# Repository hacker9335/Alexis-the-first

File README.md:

# Alexis the First

### Inspiration
I wanted to create a macropad that could help me access shortcuts I use commonly more easily. To assist with that, I added 6 keys, a rotary encoder, and some RGB for fun.

### Challenges
This was my first time using KiCad, and I had some fun figuring out how to properly use it.

### Specifications

#### BOM:
- 6x Cherry MX Switches
- 4x SK6812 MINI LEDs
- 1x Seeed XIAO RP2040
- 1x EC11 Rotary Encoder
- 6x Blank DSA Keycaps
- 4x M3x16 Bolts
- 4x M3 Heatset Inserts

#### Other Files:
- KMK Firmware (`Firmware/main.py`)
- Top Plate (`CAD/top_plate.3MF`)
- Bottom Plate (`CAD/bottom_plate.3MF`)
- Full Model Mockup (`CAD/Alexis_the_first_full.STEP`)

---

### Screenshots

| Schematic | PCB | Case |
|:---------:|:---:|:----:|
|  |  |  |

---

### Notes
- All design files are organized in their respective folders: `CAD/`, `PCB/`, `Firmware/`.
- The project uses only approved parts and fits within the required dimensions.

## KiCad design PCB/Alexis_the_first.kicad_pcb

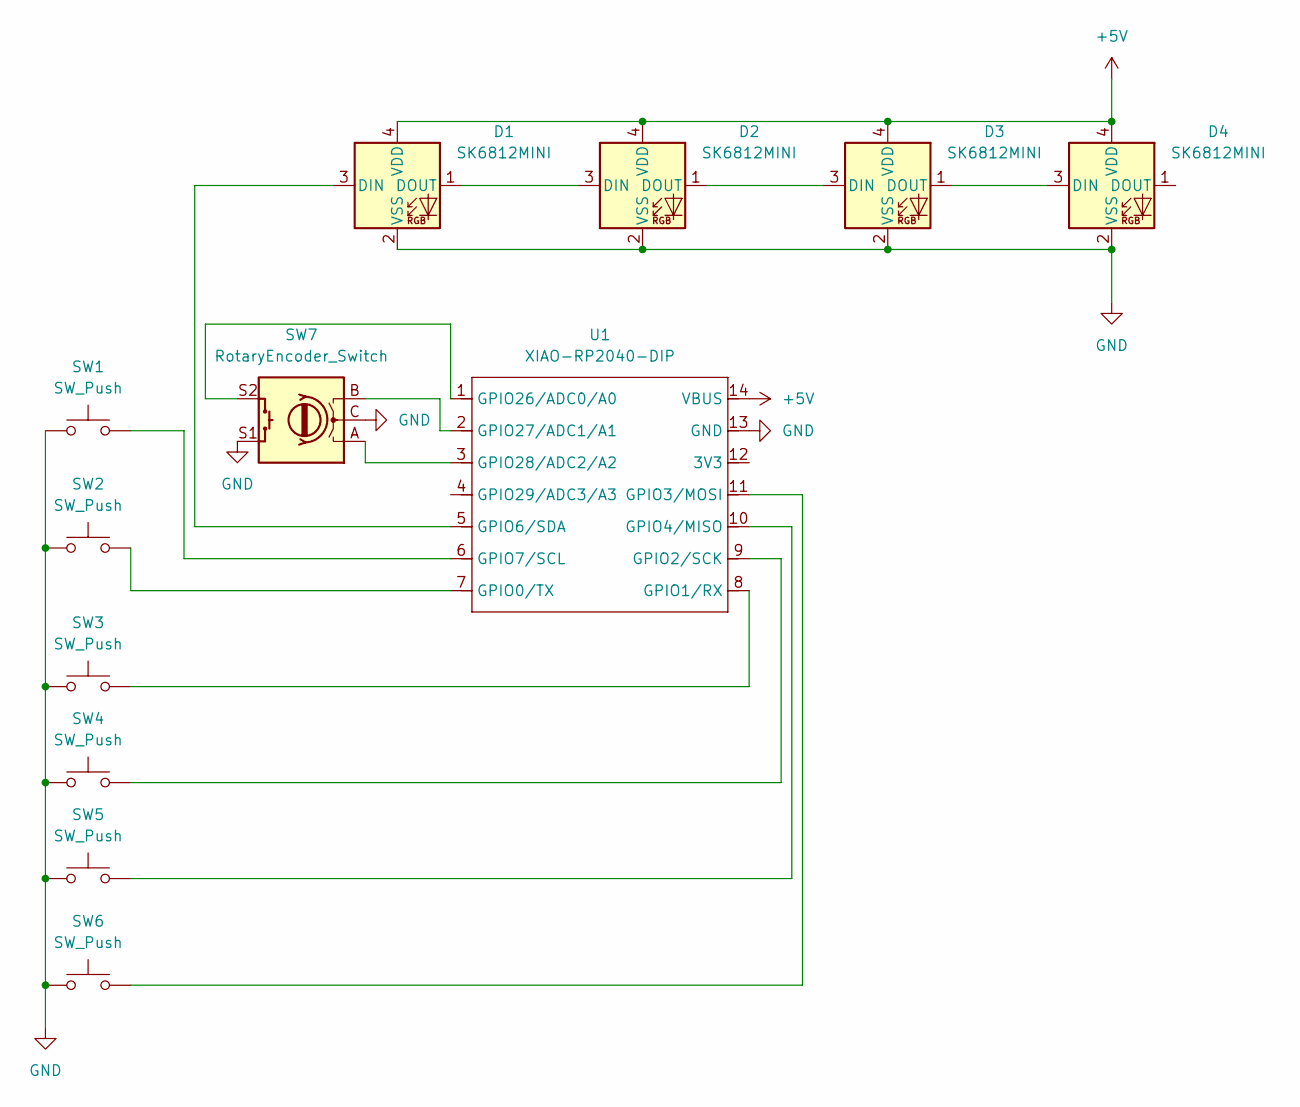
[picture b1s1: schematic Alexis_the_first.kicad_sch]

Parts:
D1, D2, D3, D4: SK6812MINI; LED_SK6812MINI_PLCC4_3.5x3.5mm_P1.75mm
SW1, SW2, SW3, SW4, SW5, SW6: SW_Push; SW_Cherry_MX_1.00u_PCB
SW7: RotaryEncoder_Switch; RotaryEncoder_Alps_EC11E-Switch_Vertical_H20mm
U1: XIAO-RP2040-DIP

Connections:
+5V: D1.4 (VDD), D2.4 (VDD), D3.4 (VDD), D4.4 (VDD), U1.14 (VBUS)
GND: D1.2 (VSS), D2.2 (VSS), D3.2 (VSS), D4.2 (VSS), SW1.1, SW2.1, SW3.1, SW4.1, SW5.1, SW6.1, SW7.C, SW7.S1, U1.13 (GND)
unnamed: D1.3 (DIN), U1.5 (GPIO6/SDA)
unnamed: D1.1 (DOUT), D2.3 (DIN)
unnamed: D2.1 (DOUT), D3.3 (DIN)
unnamed: D3.1 (DOUT), D4.3 (DIN)
unnamed: SW2.2, U1.7 (GPIO0/TX)
unnamed: SW3.2, U1.8 (GPIO1/RX)
unnamed: SW4.2, U1.9 (GPIO2/SCK)
unnamed: SW6.2, U1.11 (GPIO3/MOSI)
unnamed: SW5.2, U1.10 (GPIO4/MISO)
unnamed: SW1.2, U1.6 (GPIO7/SCL)
unnamed: SW7.S2, U1.1 (GPIO26/ADC0/A0)
unnamed: SW7.B, U1.2 (GPIO27/ADC1/A1)
unnamed: SW7.A, U1.3 (GPIO28/ADC2/A2)

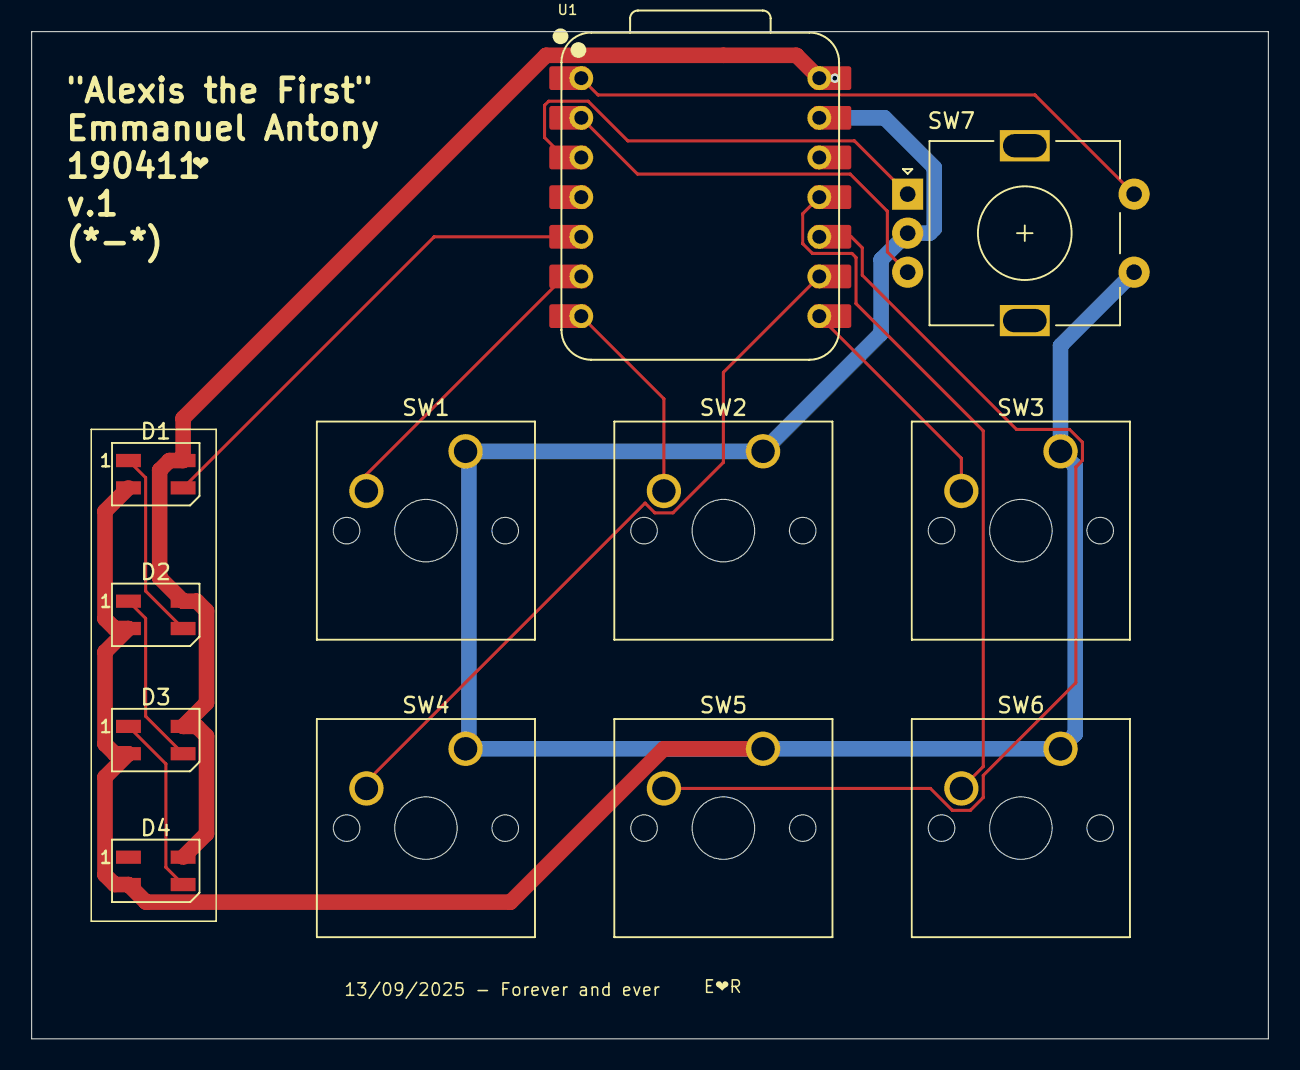
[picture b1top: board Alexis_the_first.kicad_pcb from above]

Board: 2 copper layers, 79.2 x 64.5 mm, 12 parts (0 on the bottom side), 15 nets.

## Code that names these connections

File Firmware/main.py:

import time
from kmk.kmk_keyboard import KMKKeyboard
from kmk.keys import KC
from kmk.modules.encoder import RotaryEncoder
from kmk.handlers.sequences import send_seq
from kmk.extensions.RGB import RGB
from kmk.modules.layers import Layers

keyboard = KMKKeyboard()

# ----- Layers -----
layers = Layers()
keyboard.modules.append(layers)

# ----- RGB -----
NUM_PIXELS = 4
IDLE_COLOR = (0, 0, 50)  # dim blue
FADE_DURATION = 0.5  # seconds

rgb = RGB(pin=keyboard.gpio6, num_pixels=NUM_PIXELS)
keyboard.extensions.append(rgb)
for i in range(NUM_PIXELS):
    rgb.pixels[i] = IDLE_COLOR

# Timing variables
last_button_time = 0
last_encoder_time = 0

# ----- Rotary Encoder -----
encoder = RotaryEncoder(
    pin_a=keyboard.gpio28,
    pin_b=keyboard.gpio27,
    clockwise=KC.VOLU,
    counter_clockwise=KC.VOLD,
)
keyboard.modules.append(encoder)

def encoder_callback(state):
    global last_encoder_time
    last_encoder_time = time.monotonic()
    print("Encoder turned!", state)
encoder.callback = encoder_callback

# Encoder switch → MUTE
ENCODER_SWITCH_PIN = keyboard.gpio26

# ----- Keymap / Macros -----
keyboard.keymap = [
    [
        send_seq("CTRL+Z"),   # GP7
        send_seq("CTRL+Y"),   # GP0
        send_seq("ALT+TAB"),  # GP1
        send_seq("WIN+L"),    # GP2
        send_seq("CTRL+C"),   # GP4
        send_seq("CTRL+V"),   # GP3
        KC.MUTE              # GP26
    ]
]

# ----- GPIO mapping -----
keyboard.gpio7 = keyboard.keymap[0][0]
keyboard.gpio0 = keyboard.keymap[0][1]
keyboard.gpio1 = keyboard.keymap[0][2]
keyboard.gpio2 = keyboard.keymap[0][3]
keyboard.gpio4 = keyboard.keymap[0][4]
keyboard.gpio3 = keyboard.keymap[0][5]
keyboard.gpio26 = keyboard.keymap[0][6]

# ----- Smooth Fade Helper -----
def ease_out_quad(t):
    return 1 - (1 - t)**2

# ----- RGB update function -----
def update_rgb():
    global last_button_time, last_encoder_time
    now = time.monotonic()

    event_time = max(last_button_time, last_encoder_time)
    elapsed = now - event_time
    t = min(1, elapsed / FADE_DURATION)
    fade_ratio = 1 - ease_out_quad(t)

    # Determine base color
    color = IDLE_COLOR
    if now - last_button_time < FADE_DURATION:
        color = (255, 0, 0)  # Red for button
    elif now - last_encoder_time < FADE_DURATION:
        color = (0, 255, 0)  # Green for encoder

    # Smooth fade
    r = int(color[0]*fade_ratio + IDLE_COLOR[0]*(1-fade_ratio))
    g = int(color[1]*fade_ratio + IDLE_COLOR[1]*(1-fade_ratio))
    b = int(color[2]*fade_ratio + IDLE_COLOR[2]*(1-fade_ratio))

    for i in range(NUM_PIXELS):
        rgb.pixels[i] = (r, g, b)

keyboard.on_after_scan = update_rgb

# ----- Key press callback with debug -----
def on_press(key):
    global last_button_time
    last_button_time = time.monotonic()
    print(f"Button pressed: {key}")
    return True

keyboard.key_pressed = on_press

# ----- Start KMK -----
if __name__ == "__main__":
    print("Starting keyboard with debug...")
    keyboard.go()

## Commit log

2025-12-05 Add README and design screenshots
2025-12-05 Add CAD, PCB, and Firmware files
